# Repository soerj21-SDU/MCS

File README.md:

#Software_for_Zynq_Based_Master_Controller
##Overview
This repository contains the software and drivers developed for the Zynq-based master controller as part of a bachelor's thesis project. The project aims to design and implement a master controller using the Xilinx Zynq platform, providing robust and efficient control for various applications.

##Table of Contents
-Introduction
-Features
-Installation
-Usage
-Contributing
-License
-Acknowledgements

##Introduction
The Zynq-based master controller is designed to leverage the capabilities of the Xilinx Zynq platform, combining the flexibility of an ARM processor with the power of FPGA. This project includes all necessary software and drivers to facilitate the development and deployment of applications on this platform.

##Features
-Comprehensive software suite for Zynq-based systems
-Custom drivers for various peripherals
-Example applications demonstrating key functionalities

##Acknowledgements
This project was developed as part of a bachelor's thesis at the University of Southern Denmark. Special thanks to Mikkel Wohlert Jensen and Søren Juul Jensen for their guidance and support.

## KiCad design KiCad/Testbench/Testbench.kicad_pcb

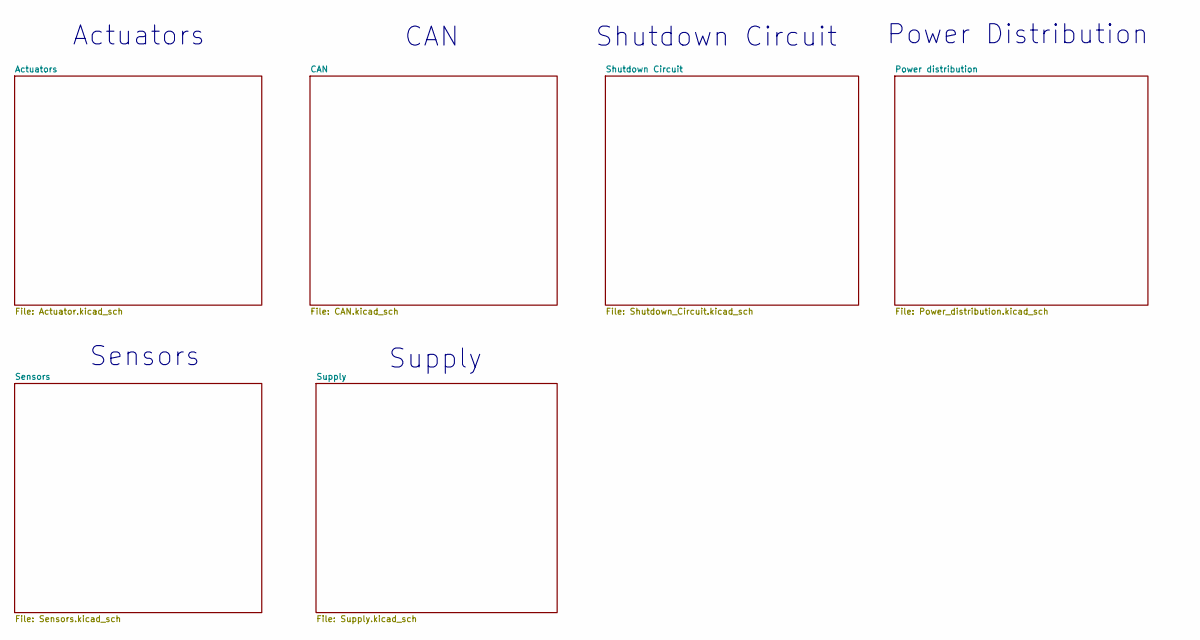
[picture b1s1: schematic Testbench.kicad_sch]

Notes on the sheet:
Shutdown Circuit
Actuators
Power Distribution
CAN
Sensors
Supply

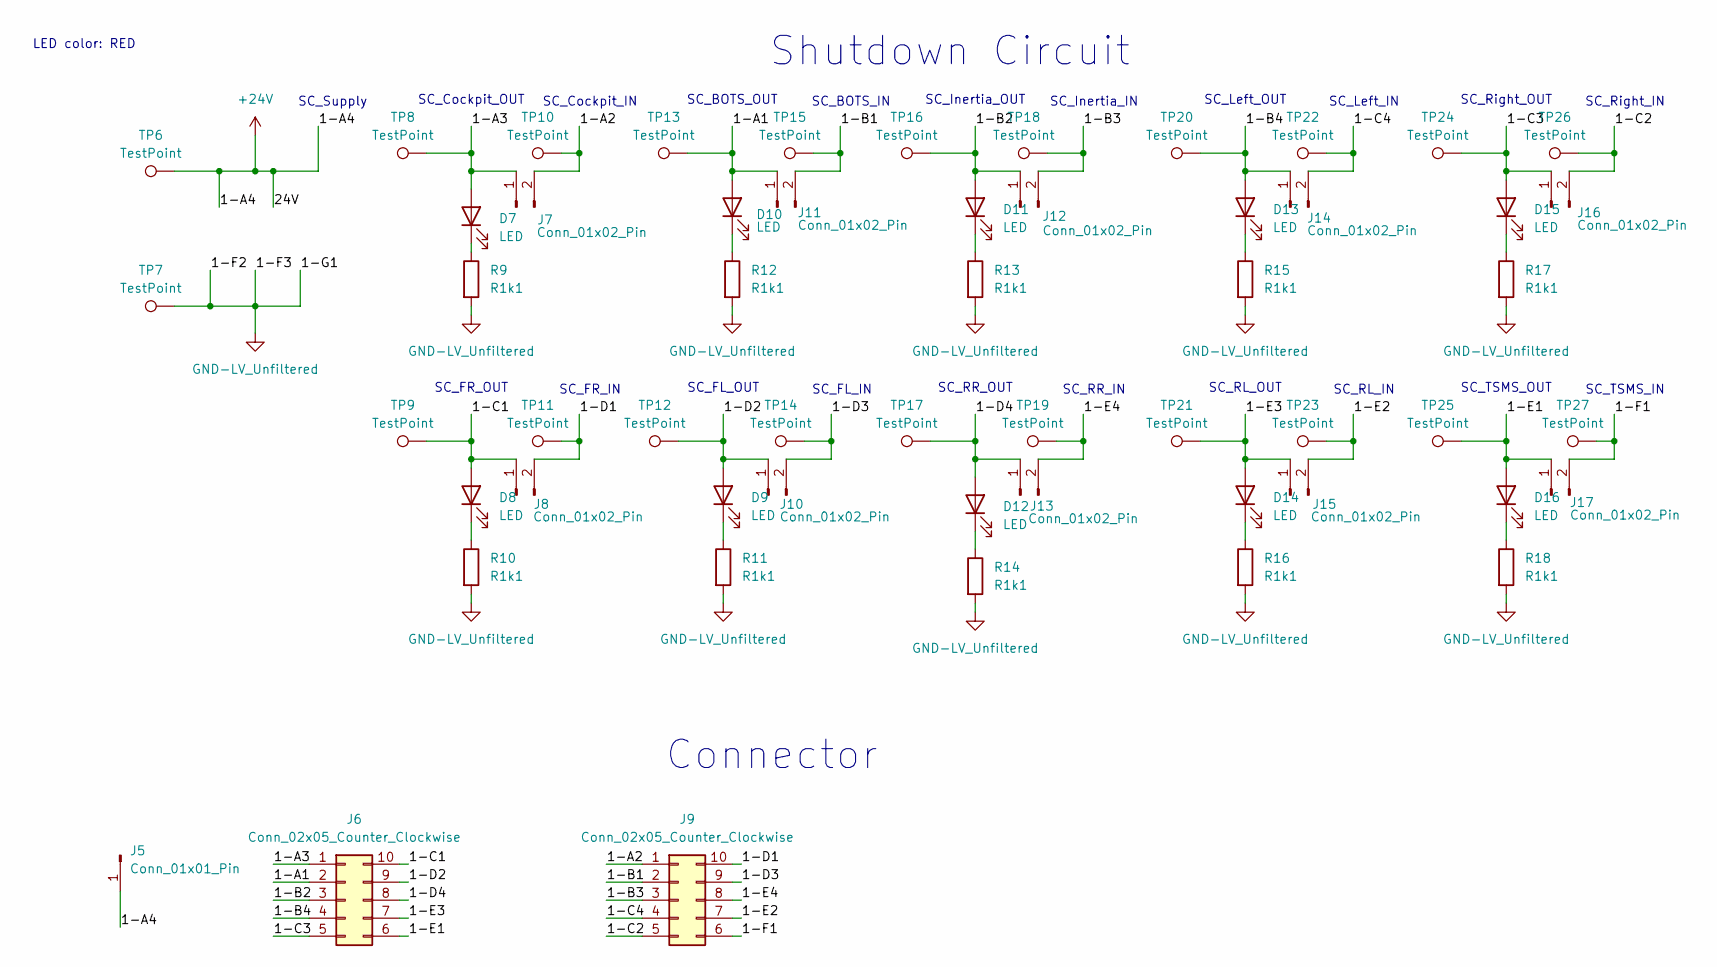
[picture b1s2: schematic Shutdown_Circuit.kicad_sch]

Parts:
D7, D8, D9, D10, D11, D12, D13, D14, D15, D16: LED; LED_0805_2012Metric_Pad1.15x1.40mm_HandSolder
J5: Conn_01x01_Pin; TestPoint_Keystone_5010-5014_Multipurpose
J6, J9: Conn_02x05_Counter_Clockwise; Molex_Mini-Fit_Jr_5566-10A_2x05_P4.20mm_Vertical
J7, J8, J10, J11, J12, J13, J14, J15, J16, J17: Conn_01x02_Pin; PinHeader_1x02_P2.54mm_Vertical
R9, R10, R11, R12, R13, R14, R15, R16, R17, R18: R1k1; R_1206_3216Metric_Pad1.30x1.75mm_HandSolder
TP6, TP7, TP8, TP9, TP10, TP11, TP12, TP13, TP14, TP15, TP16, TP17, TP18, TP19, TP20, TP21, TP22, TP23, TP24, TP25, TP26, TP27: TestPoint; TestPoint_Keystone_5010-5014_Multipurpose

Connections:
+24V: J5.1, TP6.1; also elsewhere on the board
/Shutdown Circuit/1-A1: D10.2 (A), J6.2, J11.1, TP13.1
/Shutdown Circuit/1-A2: J7.2, J9.1, TP10.1
/Shutdown Circuit/1-A3: D7.2 (A), J6.1, J7.1, TP8.1
/Shutdown Circuit/1-B1: J9.2, J11.2, TP15.1
/Shutdown Circuit/1-B2: D11.2 (A), J6.3, J12.1, TP16.1
/Shutdown Circuit/1-B3: J9.3, J12.2, TP18.1
/Shutdown Circuit/1-B4: D13.2 (A), J6.4, J14.1, TP20.1
/Shutdown Circuit/1-C1: D8.2 (A), J6.10, J8.1, TP9.1
/Shutdown Circuit/1-C2: J9.5, J16.2, TP26.1
/Shutdown Circuit/1-C3: D15.2 (A), J6.5, J16.1, TP24.1
/Shutdown Circuit/1-C4: J9.4, J14.2, TP22.1
/Shutdown Circuit/1-D1: J8.2, J9.10, TP11.1
/Shutdown Circuit/1-D2: D9.2 (A), J6.9, J10.1, TP12.1
/Shutdown Circuit/1-D3: J9.9, J10.2, TP14.1
/Shutdown Circuit/1-D4: D12.2 (A), J6.8, J13.1, TP17.1
/Shutdown Circuit/1-E1: D16.2 (A), J6.6, J17.1, TP25.1
/Shutdown Circuit/1-E2: J9.7, J15.2, TP23.1
/Shutdown Circuit/1-E3: D14.2 (A), J6.7, J15.1, TP21.1
/Shutdown Circuit/1-E4: J9.8, J13.2, TP19.1
/Shutdown Circuit/1-F1: J9.6, J17.2, TP27.1
GND-LV_Unfiltered: R9.2, R10.2, R11.2, R12.2, R13.2, R14.2, R15.2, R16.2, R17.2, R18.2, TP7.1; also elsewhere on the board
unnamed: D7.1 (K), R9.1
unnamed: D8.1 (K), R10.1
unnamed: D9.1 (K), R11.1
unnamed: D10.1 (K), R12.1
unnamed: D11.1 (K), R13.1
unnamed: D12.1 (K), R14.1
unnamed: D13.1 (K), R15.1
unnamed: D14.1 (K), R16.1
unnamed: D15.1 (K), R17.1
unnamed: D16.1 (K), R18.1

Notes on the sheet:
SC_TSMS_OUT
SC_Cockpit_IN
Shutdown Circuit
SC_Right_OUT
LED color: RED
SC_TSMS_IN
SC_FL_OUT
Connector
SC_Left_IN
SC_Supply
SC_Left_OUT
SC_RL_IN
SC_FR_OUT
SC_Right_IN
SC_FR_IN
SC_FL_IN
SC_BOTS_IN
SC_RR_OUT
SC_Inertia_OUT
SC_RL_OUT
SC_RR_IN
SC_Inertia_IN
SC_BOTS_OUT
SC_Cockpit_OUT

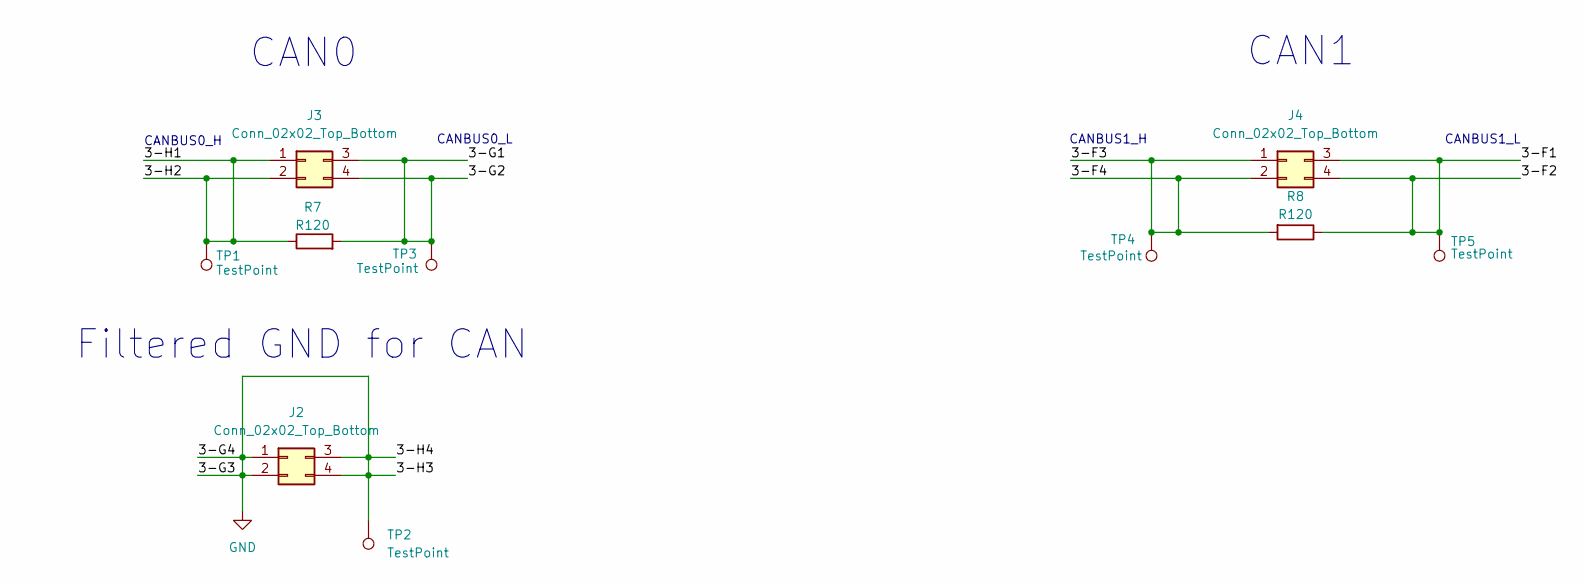
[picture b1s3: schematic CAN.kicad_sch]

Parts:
J2, J3, J4: Conn_02x02_Top_Bottom; Molex_Mini-Fit_Jr_5566-04A_2x02_P4.20mm_Vertical
R7, R8: R120; R_1206_3216Metric_Pad1.30x1.75mm_HandSolder
TP1, TP2, TP3, TP4, TP5: TestPoint; TestPoint_Keystone_5010-5014_Multipurpose

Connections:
/CAN/3-F1: J4.3, J4.4, R8.1, TP5.1
/CAN/3-F3: J4.1, J4.2, R8.2, TP4.1
/CAN/3-G1: J3.3, J3.4, R7.2, TP3.1
/CAN/3-H1: J3.1, J3.2, R7.1, TP1.1
GND: J2.1, J2.2, J2.3, J2.4, TP2.1

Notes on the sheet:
CANBUS1_L
Filtered GND for CAN
CANBUS0_H
CANBUS0_L
CAN0
CANBUS1_H
CAN1

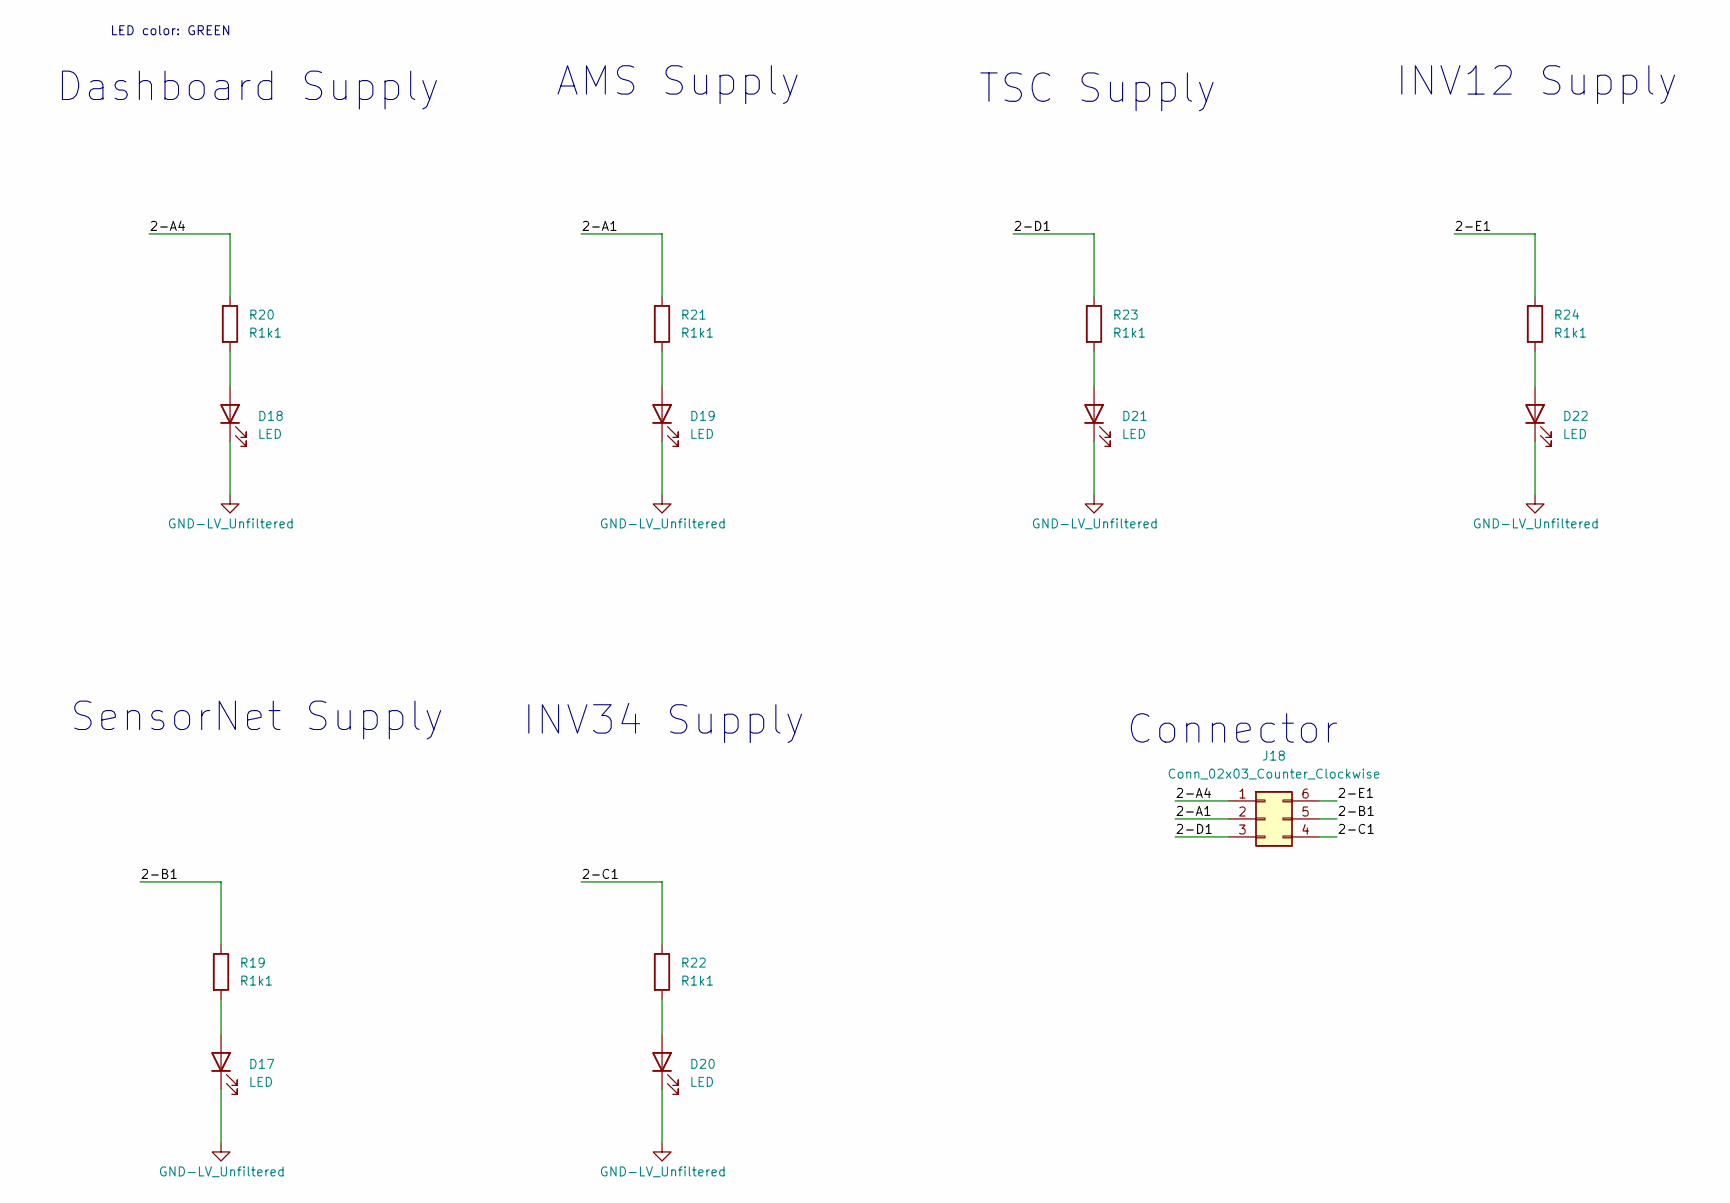
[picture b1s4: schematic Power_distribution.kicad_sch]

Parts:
D17, D18, D19, D20, D21, D22: LED; LED_0805_2012Metric_Pad1.15x1.40mm_HandSolder
J18: Conn_02x03_Counter_Clockwise; Molex_Mini-Fit_Jr_5566-06A_2x03_P4.20mm_Vertical
R19, R20, R21, R22, R23, R24: R1k1; R_1206_3216Metric_Pad1.30x1.75mm_HandSolder

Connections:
/Power distribution/2-A1: J18.2, R21.1
/Power distribution/2-A4: J18.1, R20.1
/Power distribution/2-B1: J18.5, R19.1
/Power distribution/2-C1: J18.4, R22.1
/Power distribution/2-D1: J18.3, R23.1
/Power distribution/2-E1: J18.6, R24.1
GND-LV_Unfiltered: D17.1 (K), D18.1 (K), D19.1 (K), D20.1 (K), D21.1 (K), D22.1 (K); also elsewhere on the board
unnamed: D17.2 (A), R19.2
unnamed: D18.2 (A), R20.2
unnamed: D19.2 (A), R21.2
unnamed: D20.2 (A), R22.2
unnamed: D21.2 (A), R23.2
unnamed: D22.2 (A), R24.2

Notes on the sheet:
Dashboard Supply
LED color: GREEN
INV34 Supply
INV12 Supply
TSC Supply
Connector
AMS Supply
SensorNet Supply

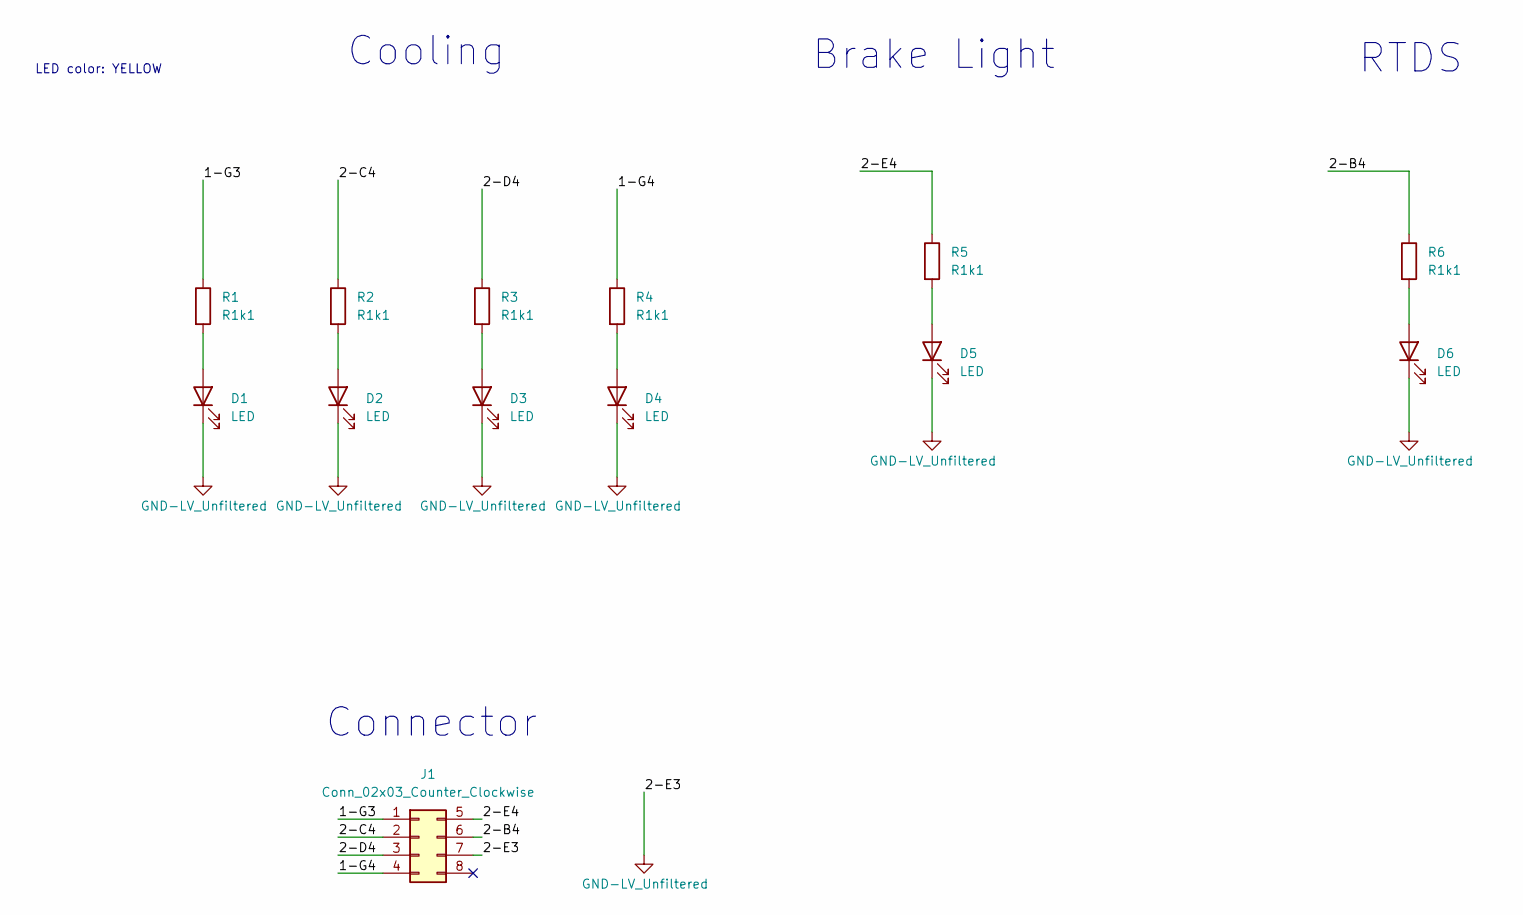
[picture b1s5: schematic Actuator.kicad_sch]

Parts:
D1, D2, D3, D4, D5, D6: LED; LED_0805_2012Metric_Pad1.15x1.40mm_HandSolder
J1: Conn_02x03_Counter_Clockwise; Molex_Mini-Fit_Jr_5566-08A_2x04_P4.20mm_Vertical
R1, R2, R3, R4, R5, R6: R1k1; R_1206_3216Metric_Pad1.30x1.75mm_HandSolder

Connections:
/Actuators/1-G3: J1.1, R1.1
/Actuators/1-G4: J1.4, R4.1
/Actuators/2-B4: J1.6, R6.1
/Actuators/2-C4: J1.2, R2.1
/Actuators/2-D4: J1.3, R3.1
/Actuators/2-E4: J1.5, R5.1
GND-LV_Unfiltered: D1.1 (K), D2.1 (K), D3.1 (K), D4.1 (K), D5.1 (K), D6.1 (K), J1.7; also elsewhere on the board
unnamed: D1.2 (A), R1.2
unnamed: D2.2 (A), R2.2
unnamed: D3.2 (A), R3.2
unnamed: D4.2 (A), R4.2
unnamed: D5.2 (A), R5.2
unnamed: D6.2 (A), R6.2

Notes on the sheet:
LED color: YELLOW
RTDS
Brake Light
Cooling
Connector

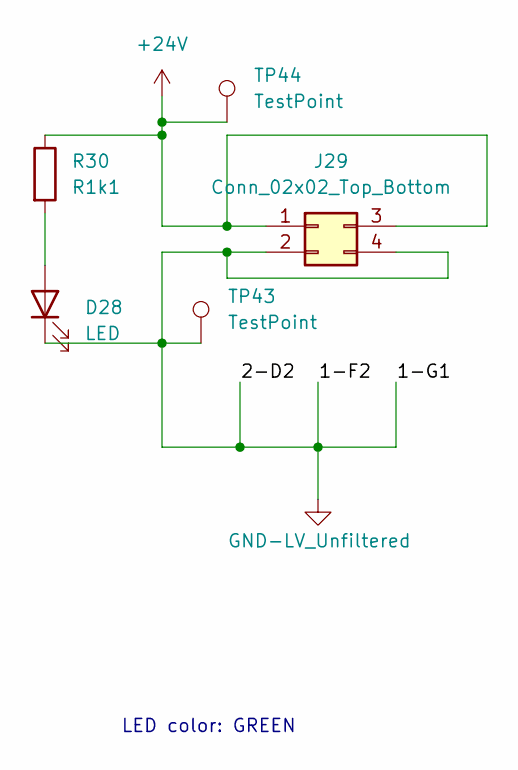
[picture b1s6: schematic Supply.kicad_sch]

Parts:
D28: LED; LED_0805_2012Metric_Pad1.15x1.40mm_HandSolder
J29: Conn_02x02_Top_Bottom; Molex_Mini-Fit_Jr_5566-04A_2x02_P4.20mm_Vertical
R30: R1k1; R_1206_3216Metric_Pad1.30x1.75mm_HandSolder
TP43, TP44: TestPoint; TestPoint_Keystone_5010-5014_Multipurpose

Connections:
+24V: J29.1, J29.3, R30.1, TP44.1; also elsewhere on the board
GND-LV_Unfiltered: D28.1 (K), J29.2, J29.4, TP43.1; also elsewhere on the board
unnamed: D28.2 (A), R30.2

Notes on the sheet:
LED color: GREEN

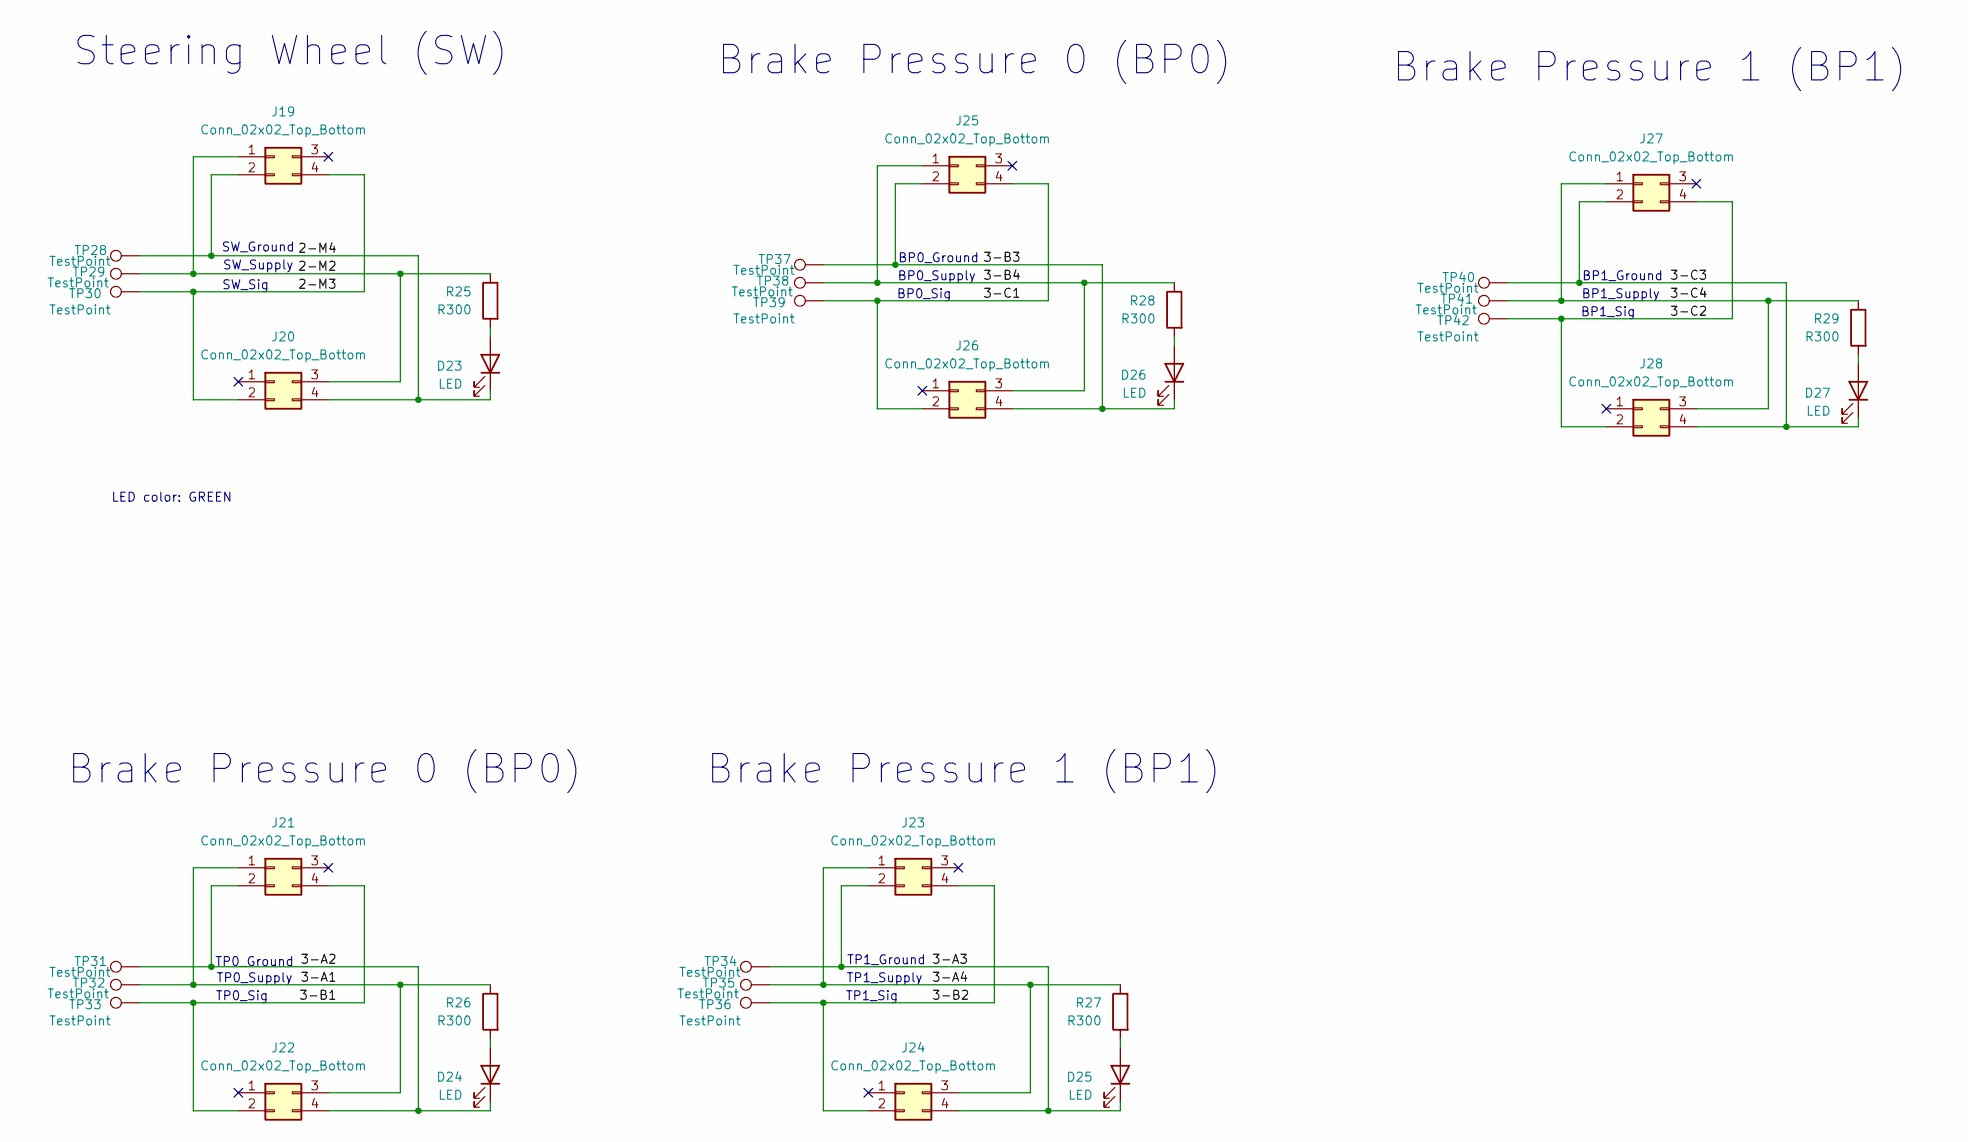
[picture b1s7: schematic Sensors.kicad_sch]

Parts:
D23, D24, D25, D26, D27: LED; LED_0805_2012Metric_Pad1.15x1.40mm_HandSolder
J19, J20, J21, J22, J23, J24, J25, J26, J27, J28: Conn_02x02_Top_Bottom; Molex_Mini-Fit_Jr_5566-04A_2x02_P4.20mm_Vertical
R25, R26, R27, R28, R29: R300; R_1206_3216Metric_Pad1.30x1.75mm_HandSolder
TP28, TP29, TP30, TP31, TP32, TP33, TP34, TP35, TP36, TP37, TP38, TP39, TP40, TP41, TP42: TestPoint; TestPoint_Keystone_5010-5014_Multipurpose

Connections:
/Sensors/2-M2: J19.1, J20.3, R25.1, TP29.1
/Sensors/2-M3: J19.4, J20.2, TP30.1
/Sensors/2-M4: D23.1 (K), J19.2, J20.4, TP28.1
/Sensors/3-A1: J21.1, J22.3, R26.1, TP32.1
/Sensors/3-A2: D24.1 (K), J21.2, J22.4, TP31.1
/Sensors/3-A3: D25.1 (K), J23.2, J24.4, TP34.1
/Sensors/3-A4: J23.1, J24.3, R27.1, TP35.1
/Sensors/3-B1: J21.4, J22.2, TP33.1
/Sensors/3-B2: J23.4, J24.2, TP36.1
/Sensors/3-B3: D26.1 (K), J25.2, J26.4, TP37.1
/Sensors/3-B4: J25.1, J26.3, R28.1, TP38.1
/Sensors/3-C1: J25.4, J26.2, TP39.1
/Sensors/3-C2: J27.4, J28.2, TP42.1
/Sensors/3-C3: D27.1 (K), J27.2, J28.4, TP40.1
/Sensors/3-C4: J27.1, J28.3, R29.1, TP41.1
unnamed: D23.2 (A), R25.2
unnamed: D24.2 (A), R26.2
unnamed: D25.2 (A), R27.2
unnamed: D26.2 (A), R28.2
unnamed: D27.2 (A), R29.2

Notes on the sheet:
BP1_Sig
SW_Supply
Brake Pressure 0 (BP0)
BP0_Supply
Brake Pressure 1 (BP1)
TP0_Sig
TP1_Ground
LED color: GREEN
TP0_Ground
BP1_Supply
BP0_Ground
TP0_Supply
SW_Ground
TP1_Sig
Steering Wheel (SW)
TP1_Supply
BP1_Ground
BP0_Sig
SW_Sig

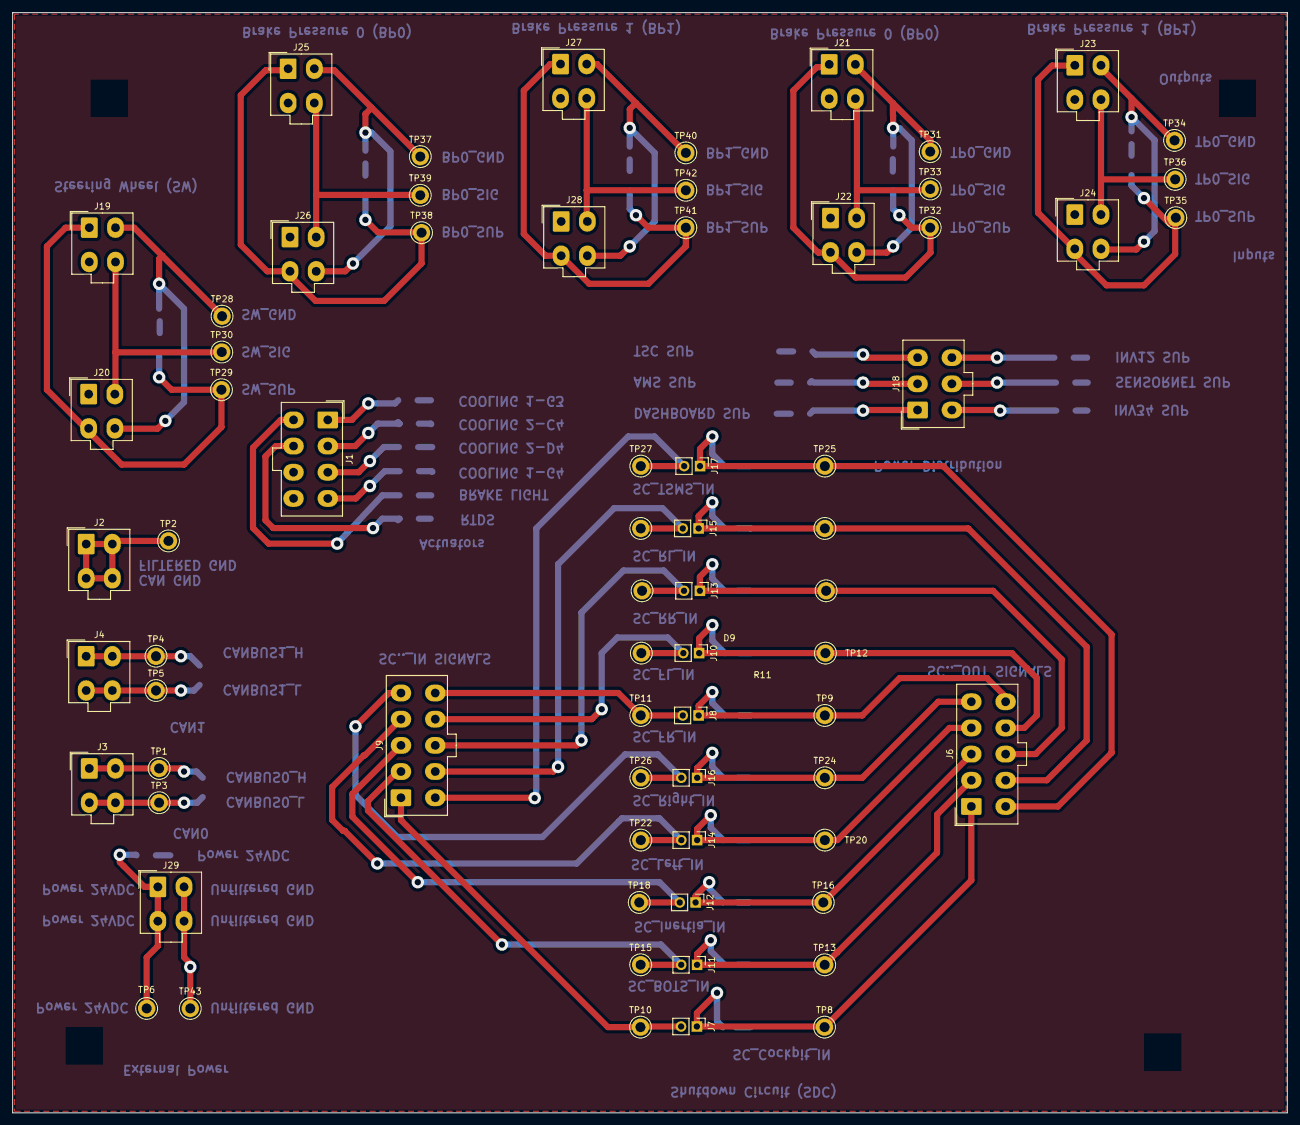
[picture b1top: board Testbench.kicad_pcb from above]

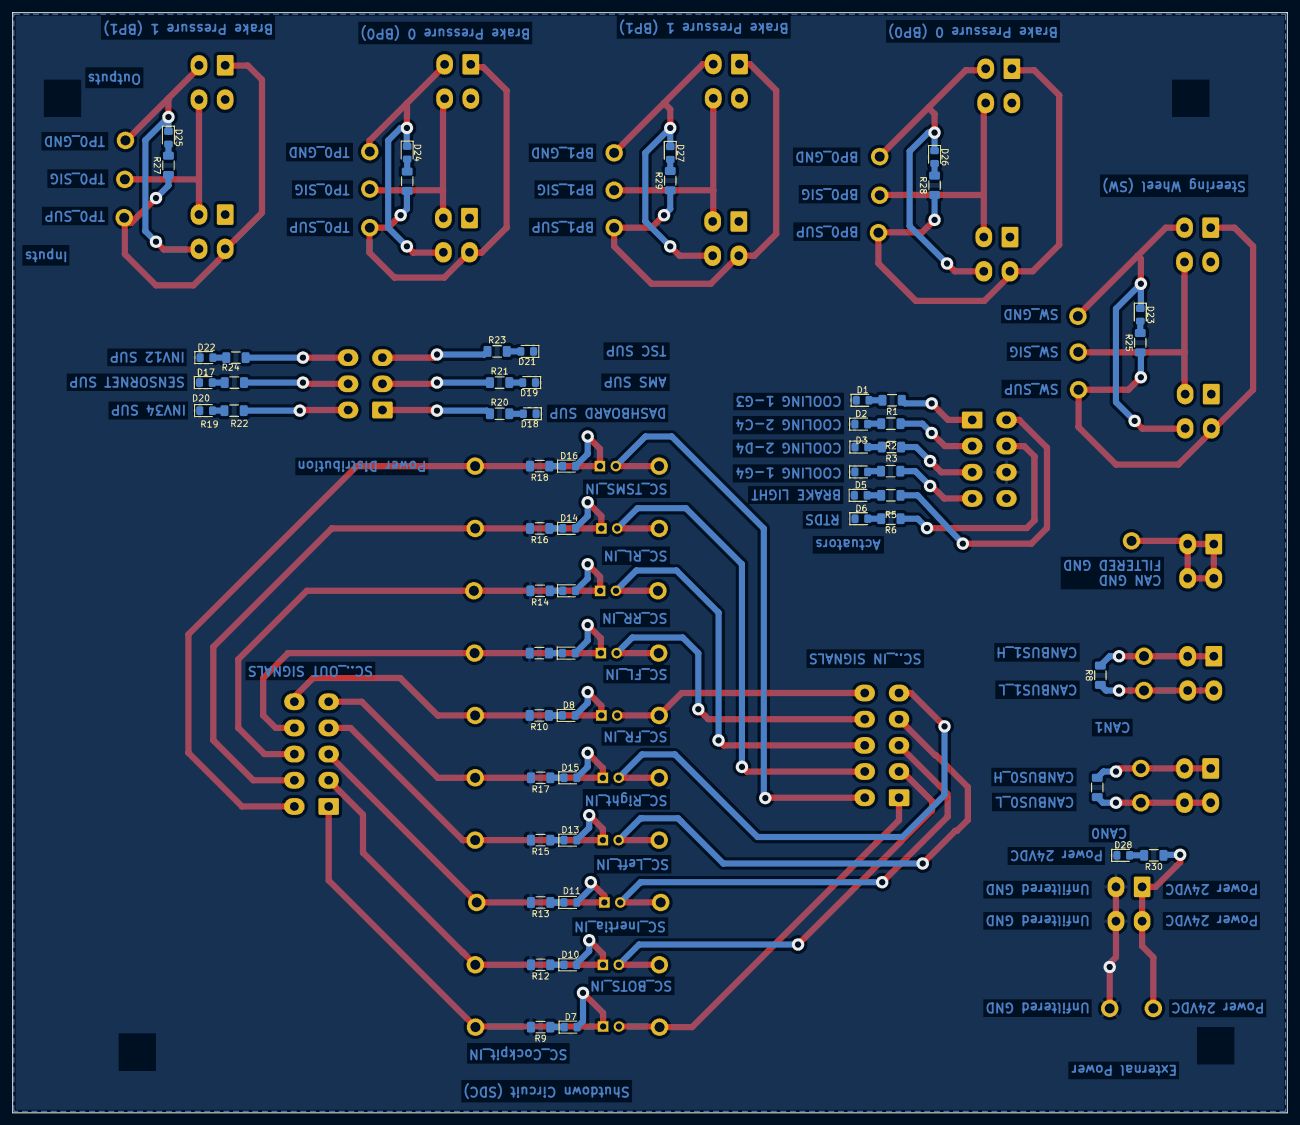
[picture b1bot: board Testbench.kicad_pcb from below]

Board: 2 copper layers, 204.5 x 176.5 mm, 128 parts (58 on the bottom side), 82 nets.

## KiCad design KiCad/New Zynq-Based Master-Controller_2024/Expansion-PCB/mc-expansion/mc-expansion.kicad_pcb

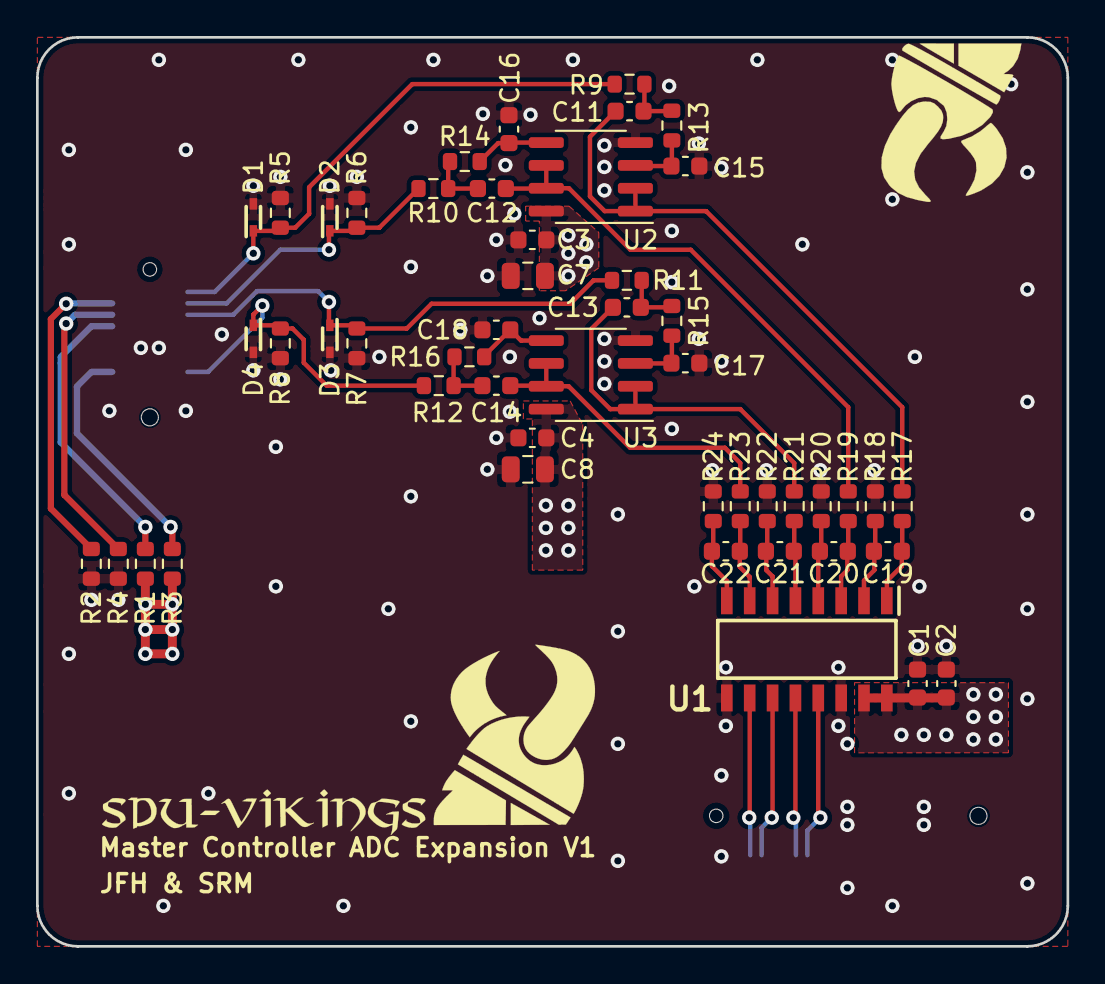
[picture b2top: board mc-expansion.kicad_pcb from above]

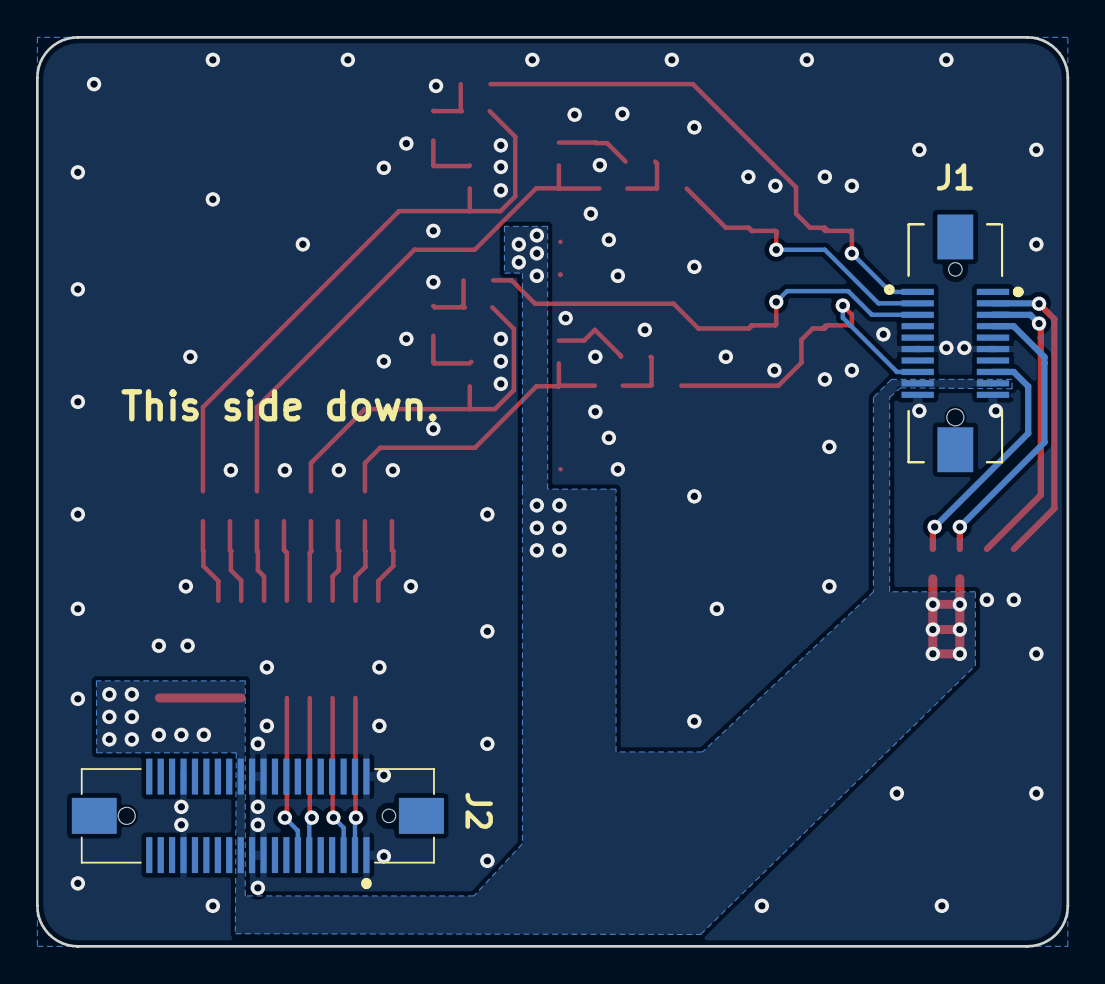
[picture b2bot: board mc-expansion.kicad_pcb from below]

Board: 2 copper layers, 57.2 x 50.5 mm, 51 parts (2 on the bottom side), 34 nets.

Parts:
C1, C3, C4: 100 nF; C_0603_1608Metric
C2: 4.7 µF; C_0603_1608Metric
C7, C8: 10 µF; C_0805_2012Metric
C11, C12, C13, C14: 56 nF; C_0603_1608Metric
C15, C16, C17, C18: 33 nF; C_0603_1608Metric
C19, C20, C21, C22: 15 nF; C_0603_1608Metric
D1, D2, D3, D4: ESD5Z5.0T1G; SODFL1608X70N
J1: Molex_53627-0274; Molex_536270274_flipped
J2: Molex_53627-0474; Molex_536270474_flipped
R1, R2, R3, R4: 0R; R_0603_1608Metric
R5, R6: 6.98k; R_0603_1608Metric
R7, R8: NC; R_0603_1608Metric
R9, R10, R11, R12, R13, R14, R15, R16: 8.66k; R_0603_1608Metric
R17, R18, R19, R20, R21, R22, R23, R24: 147 R; R_0603_1608Metric
U1: MCP6L02x-xSN; SOIC127P600X175-16N
U2, U3: MCP6L02x-xSN; SOIC-8_3.9x4.9mm_P1.27mm

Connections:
+5V: C1.2, C2.2, C3.2, C4.2, C7.2, C8.2, J1.17, J1.18, J2.23, J2.24, R1.1, R3.1, U1.15, U1.16, U2.8, U3.8
/A2_N: C21.2, R22.1, U1.6
/A2_P: C21.1, R21.1, U1.5
/A3_N: C22.2, R24.1, U1.8
/A3_P: C22.1, R23.1, U1.7
/AuxSensor2: D3.1, J1.6, R7.1, R11.2
/AuxSensor2Ground: J1.3, R2.2
/AuxSensor2Supply: J1.7, R1.2
/AuxSensor3: D4.1, J1.16, R8.1, R12.2
/AuxSensor3Ground: J1.5, R4.2
/AuxSensor3Supply: J1.15, R3.2
/CS0_N: C19.2, R18.1, U1.2
/CS0_P: C19.1, R17.1, U1.1
/CS1_N: C20.2, R20.1, U1.4
/CS1_P: C20.1, R19.1, U1.3
/CoolSensor0: D1.1, J1.2, R5.1, R9.2
/CoolSensor1: D2.1, J1.4, R6.1, R10.2
/SPI_CLK: J2.13, U1.13
/SPI_CS: J2.3, U1.10
/SPI_IN: J2.5, U1.11
/SPI_OUT: J2.11, U1.12
GND: C1.1, C2.1, C3.1, C4.1, C7.1, C8.1, C15.2, C16.2, C17.2, C18.2, D1.2, D2.2, D3.2, D4.2, J1.11, J1.12, J1.19, J1.20, J2.1, J2.2, J2.19, J2.20, J2.21, J2.22, J2.33, J2.34, R2.1, R4.1, R5.2, R6.2, R7.2, R8.2, R18.2, R20.2, R22.2, R24.2, U1.9, U1.14, U2.4, U3.4
unnamed: C11.1, R17.2, U2.1, U2.2
unnamed: C11.2, R9.1, R13.2
unnamed: C12.1, R19.2, U2.6, U2.7
unnamed: C12.2, R10.1, R14.2
unnamed: C13.1, R21.2, U3.1, U3.2
unnamed: C13.2, R11.1, R15.2
unnamed: C14.1, R23.2, U3.6, U3.7
unnamed: C14.2, R12.1, R16.2
unnamed: C15.1, R13.1, U2.3
unnamed: C16.1, R14.1, U2.5
unnamed: C17.1, R15.1, U3.3
unnamed: C18.1, R16.1, U3.5

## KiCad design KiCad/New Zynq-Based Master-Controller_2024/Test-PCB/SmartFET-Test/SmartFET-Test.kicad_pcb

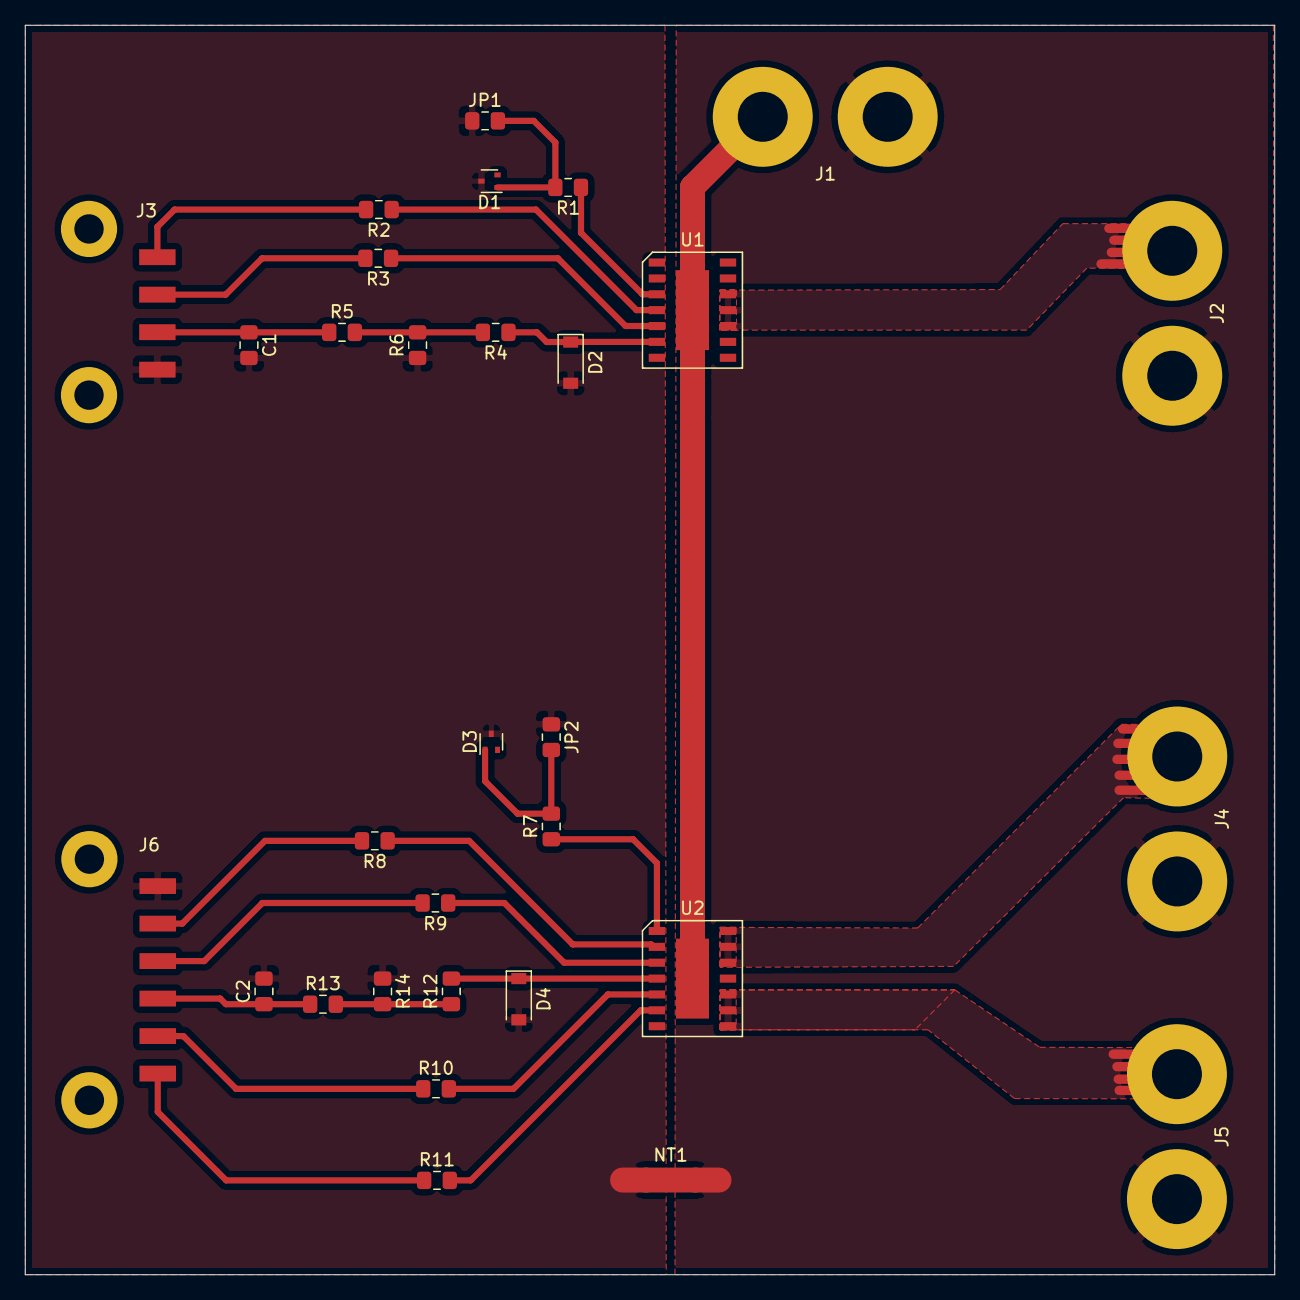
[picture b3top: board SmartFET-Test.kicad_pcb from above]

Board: 2 copper layers, 100.0 x 100.0 mm, 31 parts (0 on the bottom side), 28 nets.

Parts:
C1: 10nF; C_0805_2012Metric_Pad1.15x1.40mm_HandSolder
C2: 10n; C_0805_2012Metric_Pad1.15x1.40mm_HandSolder
D1, D3: BAS21T-7-F; SOT-523
D2, D4: D_Zener_ALT; D_SOD-123
J1, J2, J4, J5: Conn_01x02; Conn_01x02_THT_4mm
J3: Conn_01x04; Wurth_WR-MPC3_662105130822_1x04_P3.00mm_Horizontal
J6: Conn_01x06; Wurth_WR-MPC3_662106130822_1x06_P3.00mm_Horizontal
JP1, JP2: Jumper_NO_Small; R_0805_2012Metric_Pad1.15x1.40mm_HandSolder
NT1: Net-Tie_2; NetTie-2_SMD_Pad2.0mm
R1, R7: 33; R_0805_2012Metric_Pad1.15x1.40mm_HandSolder
R2, R3, R8, R9, R10, R11: 4k7; R_0805_2012Metric_Pad1.15x1.40mm_HandSolder
R4, R12: 1k5; R_0805_2012Metric_Pad1.15x1.40mm_HandSolder
R5, R13: 10k; R_0805_2012Metric_Pad1.15x1.40mm_HandSolder
R6, R14: 330; R_0805_2012Metric_Pad1.15x1.40mm_HandSolder
U1: BTT6010-1EKB; PG-DSO-14-47
U2: BTT6030-2EKA; PG-DSO-14-40

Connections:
+24V: J1.1, U1.Cool.Tab, U2.Cool.Tab
/BTT6010_OUT: J2.1, U1.10, U1.11, U1.12
/BTT6030_OUT0: J4.1, U2.12, U2.13, U2.14
/BTT6030_OUT1: J5.1, U2.8, U2.9, U2.10
/DEN_6030: J6.3, R9.2
/DSEL_6030: J6.5, R10.1
/IN0_6030: J6.2, R8.2
/IN1_6030: J6.6, R11.1
/IS_6030: D4.1, R12.2, U2.4
GND: C1.2, C2.2, D1.3, D2.2, D3.3, D4.2, J3.4, J6.1, JP1.1, JP2.1, NT1.1, R6.1, R14.1
GNDPWR: J1.2, J2.2, J4.2, J5.2, NT1.2
unnamed: C1.1, J3.3, R5.1
unnamed: C2.1, J6.4, R13.1
unnamed: D1.1, JP1.2, R1.2
unnamed: D2.1, R4.1, U1.6
unnamed: D3.1, JP2.2, R7.2
unnamed: J3.1, R2.2
unnamed: J3.2, R3.2
unnamed: R1.1, U1.3
unnamed: R2.1, U1.4
unnamed: R3.1, U1.5
unnamed: R4.2, R5.2, R6.2
unnamed: R7.1, U2.1
unnamed: R8.1, U2.2
unnamed: R9.1, U2.3
unnamed: R10.2, U2.5
unnamed: R11.2, U2.6
unnamed: R12.1, R13.2, R14.2
